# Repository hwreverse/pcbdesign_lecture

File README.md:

# pcbdesign_lecture
PCB Design Lectures Examples

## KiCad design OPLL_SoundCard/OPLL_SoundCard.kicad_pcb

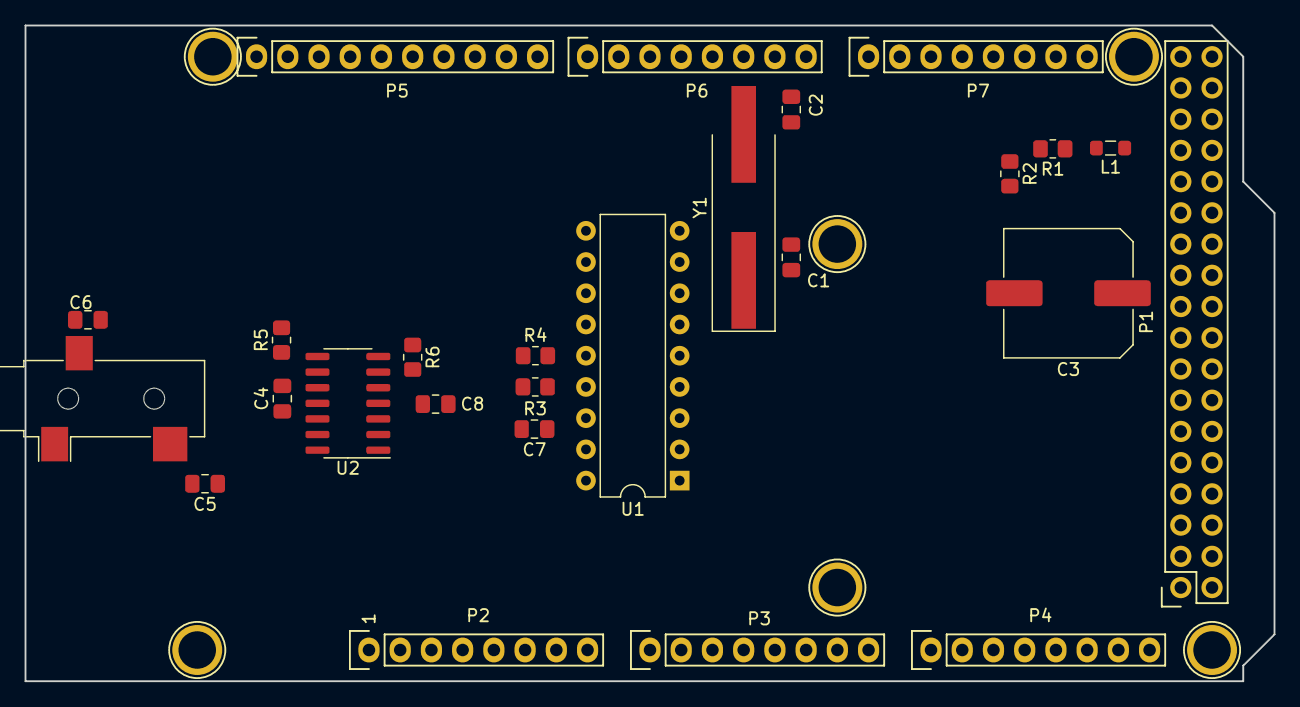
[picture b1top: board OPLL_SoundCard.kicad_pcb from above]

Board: 2 copper layers, 101.6 x 53.3 mm, 32 parts (0 on the bottom side), 28 nets, no tracks yet.

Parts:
C1, C2: 15pF; C_0805_2012Metric_Pad1.18x1.45mm_HandSolder
C3: 1000uF; C_Elec_10x10.2
C4: 15nF; C_0805_2012Metric_Pad1.18x1.45mm_HandSolder
C5, C6: 10uF; C_0805_2012Metric_Pad1.18x1.45mm_HandSolder
C7, C8: .1uF; C_0805_2012Metric_Pad1.18x1.45mm_HandSolder
J1: AudioJack3; Jack_3.5mm_CUI_SJ-3523-SMT_Horizontal
L1: 1mH; L_0805_2012Metric_Pad1.05x1.20mm_HandSolder
P1: Digital; Socket_Strip_Arduino_2x18
P2: Power; Socket_Strip_Arduino_1x08
P3, P4: Analog; Socket_Strip_Arduino_1x08
P5: PWM; Socket_Strip_Arduino_1x10
P6: PWM; Socket_Strip_Arduino_1x08
P7: Communication; Socket_Strip_Arduino_1x08
P8, P9, P10, P11, P12, P13: CONN_01X01; Arduino_1pin
R1: 10k; R_0805_2012Metric_Pad1.20x1.40mm_HandSolder
R2, R5: 4k7; R_0805_2012Metric_Pad1.20x1.40mm_HandSolder
R3, R4, R6: 2.2k; R_0805_2012Metric_Pad1.20x1.40mm_HandSolder
U1: YM2413B; DIP-18_W7.62mm
U2: LMC660; SOIC-14_3.9x8.7mm_P1.27mm
Y1: 3.57MHz; Crystal_SMD_HC49-SD_HandSoldering

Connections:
+5V: C7.1, C8.1, L1.1, P1.35, P1.36, P2.5, U1.16, U2.4
/A0: P3.1, U1.10
/D0: P4.1, U1.17
/D1: P4.2, U1.18
/D2: P4.3, U1.2
/D3: P4.4, U1.3
/D4: P4.5, U1.4
/D5: P4.6, U1.5
/D6: P4.7, U1.6
/D7: P4.8, U1.7
/~CS: P3.2, U1.12
/~IC: P3.3, U1.13
/~WE: P3.4, U1.11
GND: C1.2, C2.2, C3.2, C4.1, C7.2, C8.2, J1.S, P1.1, P1.2, P2.6, P2.7, P5.4, R2.2, U1.1, U2.11
unnamed: C1.1, U1.8, Y1.1
unnamed: C2.1, U1.9, Y1.2
unnamed: C3.1, L1.2, R1.1
unnamed: C4.2, R5.1, U2.3, U2.10
unnamed: C5.1, U2.1, U2.2
unnamed: C5.2, J1.T
unnamed: C6.1, U2.8, U2.9
unnamed: C6.2, J1.R
unnamed: R3.1, R4.1, R6.2, U2.6
unnamed: R3.2, U1.15
unnamed: R4.2, U1.14
unnamed: R5.2, R6.1, U2.7
unnamed: U2.5, U2.13, U2.14
VREG: R1.2, R2.1, U2.12

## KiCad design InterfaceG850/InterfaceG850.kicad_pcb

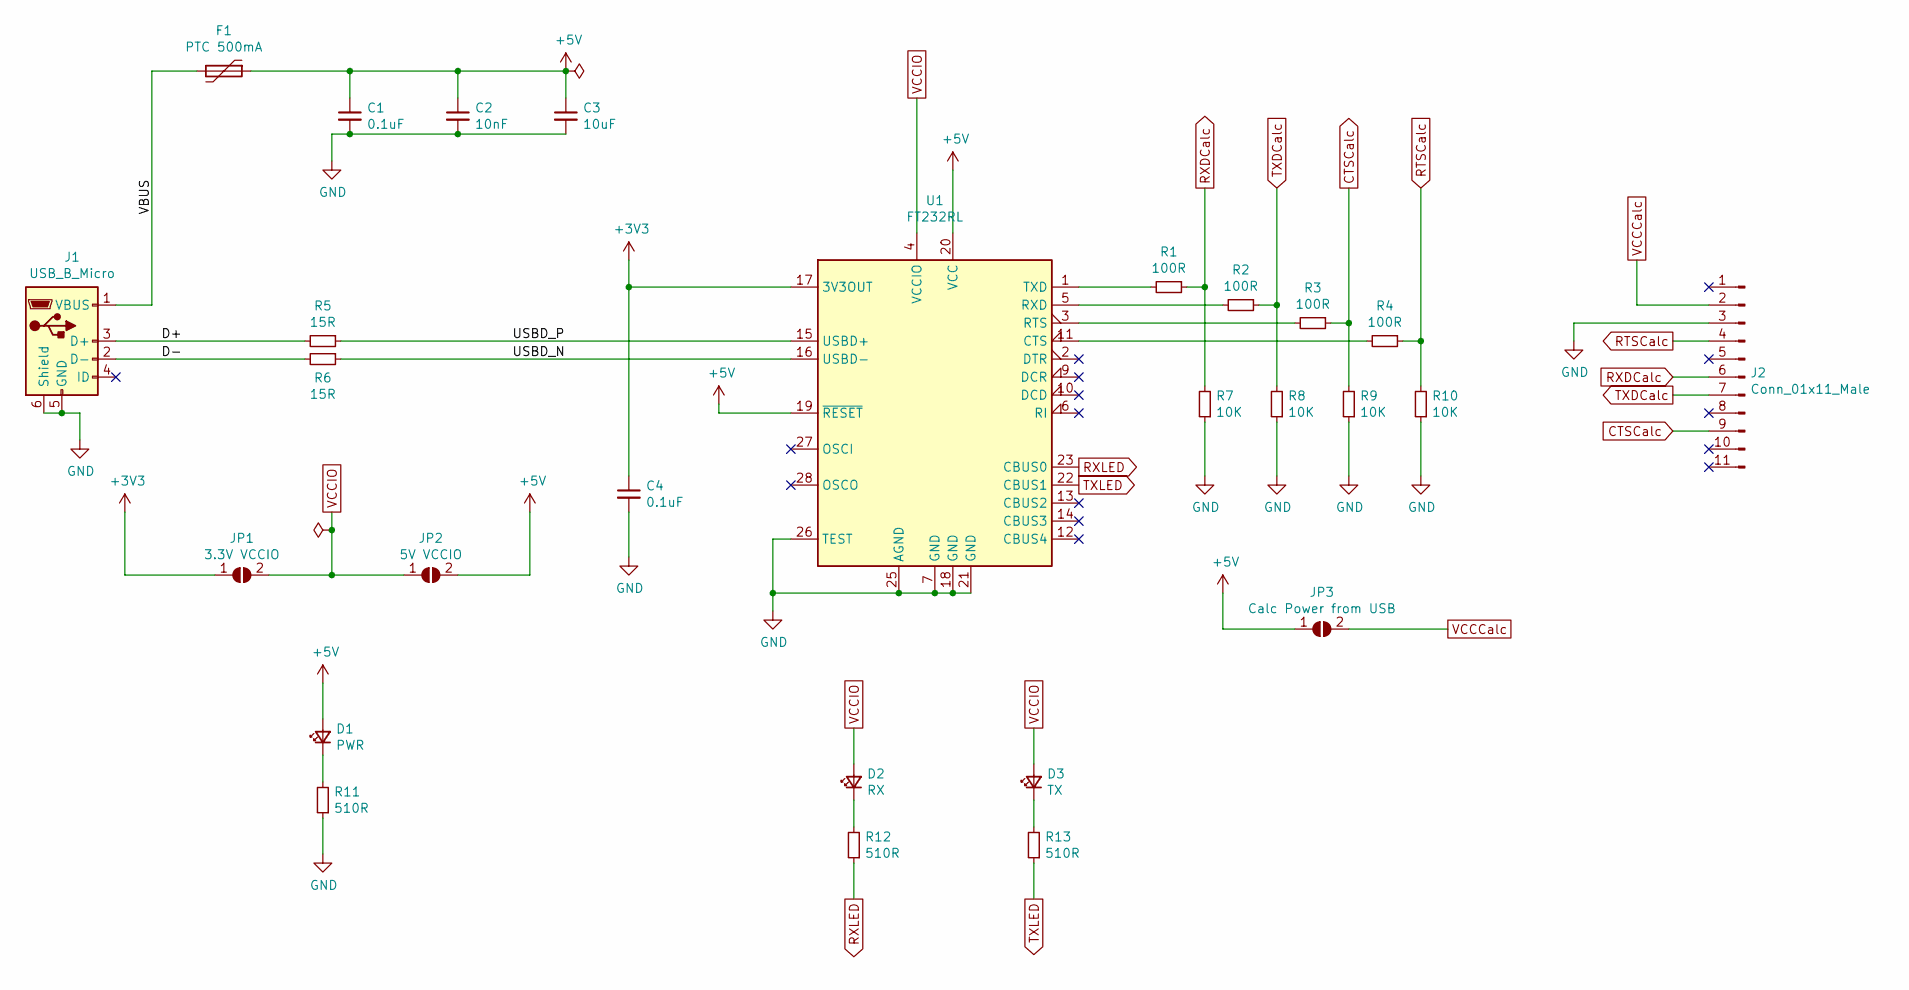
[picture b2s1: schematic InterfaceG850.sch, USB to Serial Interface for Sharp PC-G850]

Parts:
C1, C4: 0.1uF; C_0805_2012Metric_Pad1.18x1.45mm_HandSolder
C2: 10nF; C_0805_2012Metric_Pad1.18x1.45mm_HandSolder
C3: 10uF; C_0805_2012Metric_Pad1.18x1.45mm_HandSolder
D1: PWR; LED_0805_2012Metric_Pad1.15x1.40mm_HandSolder
D2: RX; LED_0805_2012Metric_Pad1.15x1.40mm_HandSolder
D3: TX; LED_0805_2012Metric_Pad1.15x1.40mm_HandSolder
F1: PTC 500mA; R_1210_3225Metric_Pad1.30x2.65mm_HandSolder
J1: USB_B_Micro; USB_Micro-B_Molex-105017-0001
J2: Conn_01x11_Male; PinHeader_1x11_P2.54mm_Vertical
JP1: 3.3V VCCIO; SolderJumper-2_P1.3mm_Open_RoundedPad1.0x1.5mm
JP2: 5V VCCIO; SolderJumper-2_P1.3mm_Open_RoundedPad1.0x1.5mm
JP3: Calc Power from USB; SolderJumper-2_P1.3mm_Open_RoundedPad1.0x1.5mm
R1, R2, R3, R4: 100R; R_0805_2012Metric_Pad1.20x1.40mm_HandSolder
R5, R6: 15R; R_0805_2012Metric_Pad1.20x1.40mm_HandSolder
R7, R8, R9, R10: 10K; R_0805_2012Metric_Pad1.20x1.40mm_HandSolder
R11, R12, R13: 510R; R_0805_2012Metric_Pad1.20x1.40mm_HandSolder
U1: FT232RL; SSOP-28_5.3x10.2mm_P0.65mm

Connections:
+3V3: C4.1, JP1.1 (A), U1.17 (3V3OUT)
+5V: C1.1, C2.1, C3.1, D1.2 (A), F1.1, JP2.2 (B), JP3.1 (A), U1.19 (~RESET~), U1.20 (VCC)
/D+: J1.3 (D+), R5.2
/D-: J1.2 (D-), R6.2
/USBD_N: R6.1, U1.16 (USBD-)
/USBD_P: R5.1, U1.15 (USBD+)
/VBUS: F1.2, J1.1 (VBUS)
CTSCalc: J2.9, R3.1, R9.2
GND: C1.2, C2.2, C3.2, C4.2, J1.5 (GND), J1.6 (Shield), J2.3, R7.1, R8.1, R9.1, R10.1, R11.1, U1.7 (GND), U1.18 (GND), U1.21 (GND), U1.25 (AGND), U1.26 (TEST)
unnamed: D1.1 (K), R11.2
unnamed: D2.1 (K), R12.2
unnamed: D3.1 (K), R13.2
unnamed: R1.2, U1.1 (TXD)
unnamed: R2.2, U1.5 (RXD)
unnamed: R3.2, U1.3 (RTS)
unnamed: R4.2, U1.11 (CTS)
RTSCalc: J2.4, R4.1, R10.2
RXDCalc: J2.6, R1.1, R7.2
RXLED: R12.1, U1.23 (CBUS0)
TXDCalc: J2.7, R2.1, R8.2
TXLED: R13.1, U1.22 (CBUS1)
VCCCalc: J2.2, JP3.2 (B)
VCCIO: D2.2 (A), D3.2 (A), JP1.2 (B), JP2.1 (A), U1.4 (VCCIO)

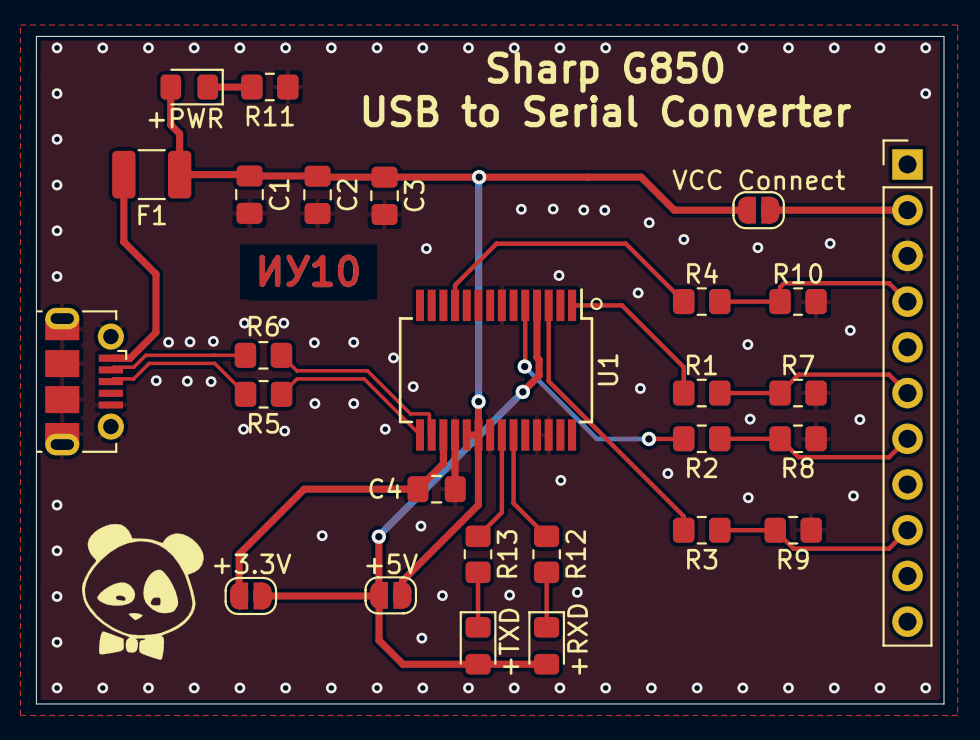
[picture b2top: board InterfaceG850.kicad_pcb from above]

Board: 2 copper layers, 50.4 x 37.1 mm, 27 parts (0 on the bottom side), 23 nets.

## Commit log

2020-09-15 fisrt commit
2020-11-10 lection 3
2020-11-13 InterfaceG850 first commit
2020-11-17 Added FT232R Datasheet
2020-11-17 Schema Ready
2020-11-17 Added Footprints
2020-11-17 added step model
2020-11-20 Added USB Signal picture
2020-11-20 lecture commit
2020-11-24 24.11.2020
2020-11-25 added dimensions
2020-11-27 27.11
2020-12-04 Panda
2020-12-04 New OPLL Soundcard
2020-12-08 Docs for OPLL Soundcard
2020-12-08 08.12.2020
2020-12-11 added Cryptoduino01 test
2020-12-11 update cryptuino01
2020-12-11 11.12.2020
    Lecture #11
2020-12-15 Added Knowledgetest 01 / 2020
2020-12-15 15.12.2020 - Lecture - OPLL schema done
2020-12-17 atted models in g850
2020-12-18 mapping
2020-12-18 PCB Soundcard
2020-12-20 Corrected error (2 pullups on D6)
    Corrected error : 2 pull-ups on D6 , none on D7
2020-12-21 Answer sheet to the questions !
